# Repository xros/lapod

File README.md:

# LaPOD
LaPOD is a project to create a logic analyzer probe for the various [Rigol]
oscilloscopes that feature the logic analyzer connector. Not all scopes have
the connector exposed and not all scopes have the components needed on the
PCB. But for those that do, the LaPOD could be a cheap alternative to get
those probes.

## Scope support
Currently supported is the MSO5000 series, which feature a 50 pin IDC connector
and the DHO900, which features the same 50 pin connector, but is a bit more
narrow at the front. To cater for either needs or choice, there's two breakout
boards that feature either a full, but wider HDMI connector, or a mini HDMI
connector which makes the PCB as narrow as possible.

The idea is, to also get a 68 pin IDC connector added, but that requires
the knowledge of the pinout and someone that can validate and test the design.
The 68 pin IDC connector should have nearly the same signals however and would
fit the DS1074Z-S Plus for example.

The DS7000 and MSO8000 feature a PCI express 1x connector (34 pins), with an
unknown pinout, but the idea is that it could very much also support our pods.

## PODs
Currently, there are 3 pods available. The LMH7322 based pod, where two dual
channel chips supply 4 bits to the pod. The LMH7322 is the same chip used in
the official PLA2216 (MSO5000) and RPL1116 (DS1000Z) probes. It may also be
used on the RPL2316 (DS2000, DS7000 and MSO8000). The original probe needs 8
of these chips for 16 channels, and that brings the cost of the chips alone
up to around $75. Probably one of the reason of the high price.

Then there's also the LMH7324 based pod. Here a single quad channel chip is
used to supply the 4 bits to the pod. The LMH7324 is very closely related to
the LMH7322, but not identical. It is a little bit cheaper option and for some
signal scenarios even preferred to have the same chip handle 4 channels.

Finally, there is the SNV65LVDS based chip. It is a much cheaper chip that can
do logic signal detection, but at a very much more limited range. It also costs
considerably less. A true cheap alternative.

## Outputs
The schematics, PCB's gerbers etc are generated by the CI pipeline and can be
found under [releases](https://gitlab.com/riglol/lapod/-/releases) for tagged
builds. Tagging happens after verification however, so the release-candidates,
the files sent out to the board house for verification can be found under
[packages](https://gitlab.com/riglol/lapod/-/packages).

## Contact
Discussion about the development of these pods is held over on the
[EEVBlog forum].

[Rigol]: https://rigolna.com
[EEVBlog forum]: https://www.eevblog.com/forum/testgear/another-low-cost-la-probe-for-rigol-mso5000-by-oliv3r/

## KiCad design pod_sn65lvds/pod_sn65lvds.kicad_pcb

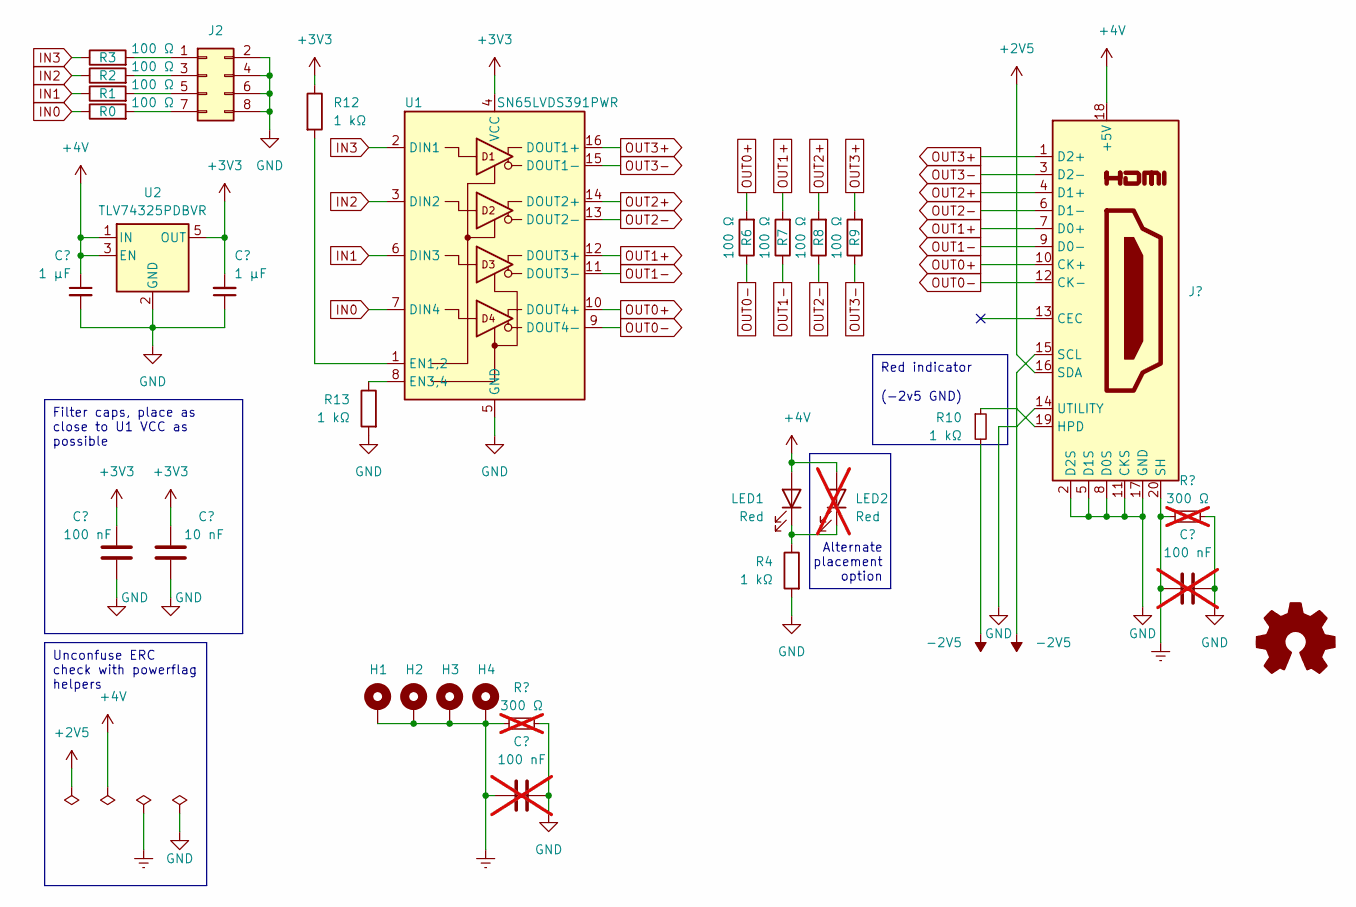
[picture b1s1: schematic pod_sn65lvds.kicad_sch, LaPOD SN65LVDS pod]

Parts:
C1, C4: 1 μF; C_0805_2012Metric_Pad1.18x1.45mm_HandSolder; tolerance 10%; LCSC C28323
C2: 100 nF; C_0805_2012Metric_Pad1.18x1.45mm_HandSolder; tolerance 10%; LCSC C49678
C3: 10 nF; C_0805_2012Metric_Pad1.18x1.45mm_HandSolder; tolerance 10%; LCSC C1710
C5, C6: 100 nF; C_0603_1608Metric_Pad1.08x0.95mm_HandSolder; tolerance 10%; LCSC C14663; not fitted
H1, H2, H3, H4: MountingHole_Pad; MountingHole_2.2mm_M2_Pad_Via
J1: HDMI_A; HDMI-SMD_HDMI-19PIN-043; LCSC C2858275
J2: Conn_02x04_Odd_Even; IDC-Header_2x04_P2.54mm_Horizontal; LCSC C9139
LED1: Red; LED_0805_2012Metric_Pad1.15x1.40mm_HandSolder; LCSC C84256
LED2: Red; LED_0805_2012Metric_Pad1.15x1.40mm_HandSolder; LCSC C84256; not fitted
R0, R1, R2, R3, R6, R7, R8, R9: 100 Ω; R_0805_2012Metric_Pad1.20x1.40mm_HandSolder; tolerance 1%; LCSC C17408
R4, R10, R12, R13: 1 kΩ; R_0805_2012Metric_Pad1.20x1.40mm_HandSolder; tolerance 1%; LCSC C17513
R5, R11: 300 Ω; R_0402_1005Metric_Pad0.72x0.64mm_HandSolder; tolerance 1%; LCSC C25102; not fitted
U1: SN65LVDS391PWR; TSSOP-16_4.4x5mm_P0.65mm; LCSC C354139
U2: TLV74325PDBVR; SOT-23-5_HandSoldering; LCSC C485154

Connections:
+2V5: J1.16 (SDA)
+3V3: C2.1, C3.1, C4.2, R12.1, U1.4 (VCC), U2.5 (OUT)
+4V: C1.1, J1.18 (+5V), LED1.2 (A), LED2.2 (A), U2.1 (IN), U2.3 (EN)
-2V5: J1.15 (SCL), R10.2
Earth: C5.2, C6.2, H1.1, H2.1, H3.1, H4.1, J1.20 (SH), R5.2, R11.2
GND: C1.2, C2.2, C3.2, C4.1, C5.1, C6.1, J1.2 (D2S), J1.5 (D1S), J1.8 (D0S), J1.11 (CKS), J1.14 (UTILITY), J1.17 (GND), J2.2, J2.4, J2.6, J2.8, R4.2, R5.1, R11.1, R13.2, U1.5 (GND), U2.2 (GND)
IN0: R0.1, U1.7 (DIN4)
IN1: R1.1, U1.6 (DIN3)
IN2: R2.1, U1.3 (DIN2)
IN3: R3.1, U1.2 (DIN1)
unnamed: J1.19 (HPD), R10.1
unnamed: J2.1, R3.2
unnamed: J2.3, R2.2
unnamed: J2.5, R1.2
unnamed: J2.7, R0.2
unnamed: LED1.1 (K), LED2.1 (K), R4.1
unnamed: R12.2, U1.1 (EN1,2)
unnamed: R13.1, U1.8 (EN3,4)
OUT0+: J1.10 (CK+), R6.2, U1.10 (DOUT4+)
OUT0-: J1.12 (CK-), R6.1, U1.9 (DOUT4-)
OUT1+: J1.7 (D0+), R7.2, U1.12 (DOUT3+)
OUT1-: J1.9 (D0-), R7.1, U1.11 (DOUT3-)
OUT2+: J1.4 (D1+), R8.2, U1.14 (DOUT2+)
OUT2-: J1.6 (D1-), R8.1, U1.13 (DOUT2-)
OUT3+: J1.1 (D2+), R9.2, U1.16 (DOUT1+)
OUT3-: J1.3 (D2-), R9.1, U1.15 (DOUT1-)

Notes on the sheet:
Alternate placement option
Red indicator (-2v5 GND)
Filter caps, place as close to U1 VCC as possible
Unconfuse ERC check with powerflag helpers

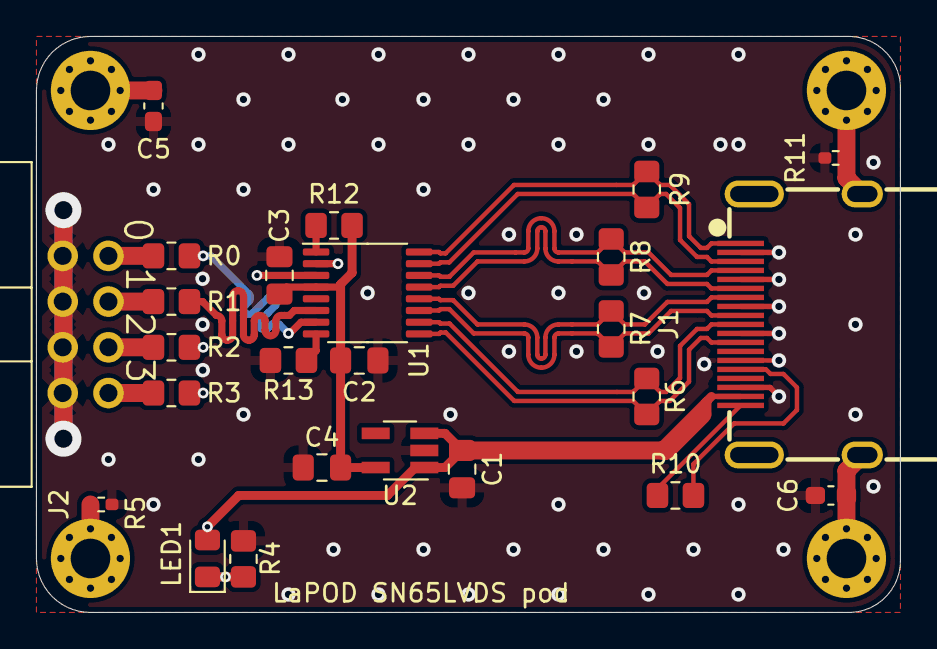
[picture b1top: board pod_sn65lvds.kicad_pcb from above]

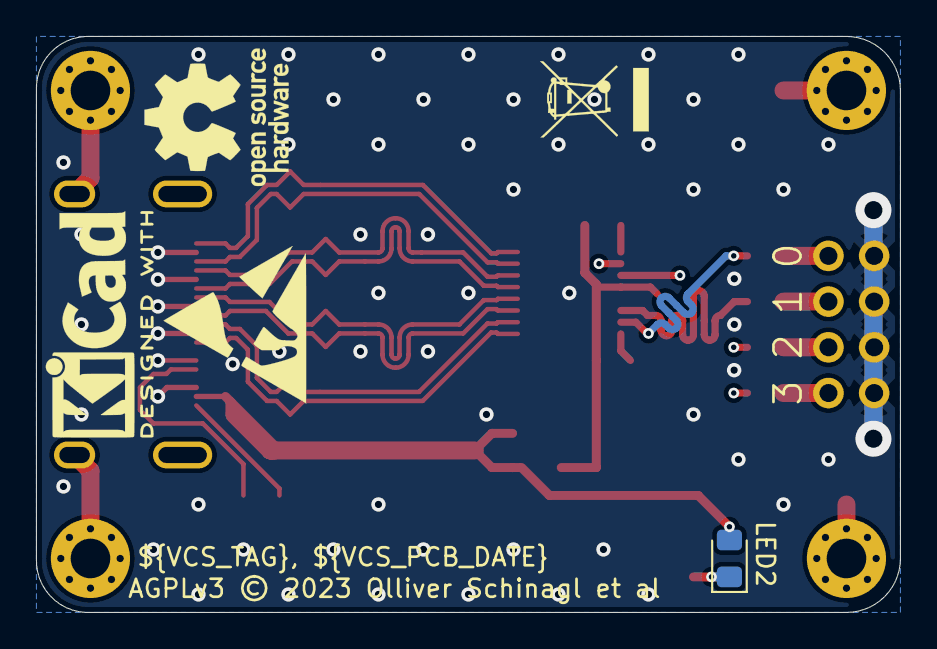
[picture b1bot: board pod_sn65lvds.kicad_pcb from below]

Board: 4 copper layers, 48.0 x 32.0 mm, 34 parts (5 on the bottom side), 25 nets.

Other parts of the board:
LG1: ESD-Logo_8.9x8mm_SilkScreen
LG2: KiCad-Logo2_5mm_SilkScreen
LG3: OSHW-Logo_7.5x8mm_SilkScreen
LG4: WEEE-Logo_4.2x6mm_SilkScreen

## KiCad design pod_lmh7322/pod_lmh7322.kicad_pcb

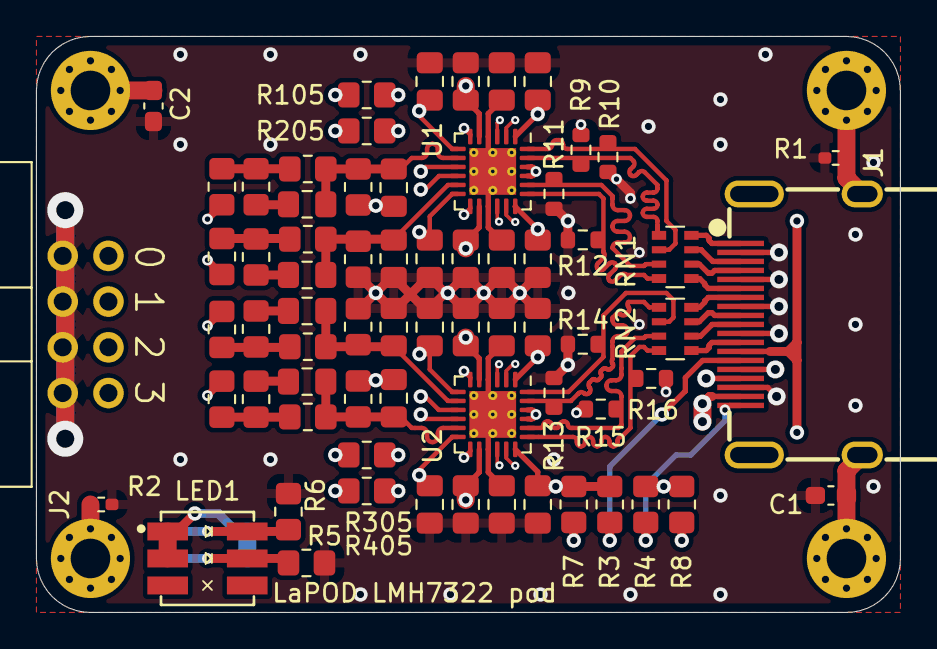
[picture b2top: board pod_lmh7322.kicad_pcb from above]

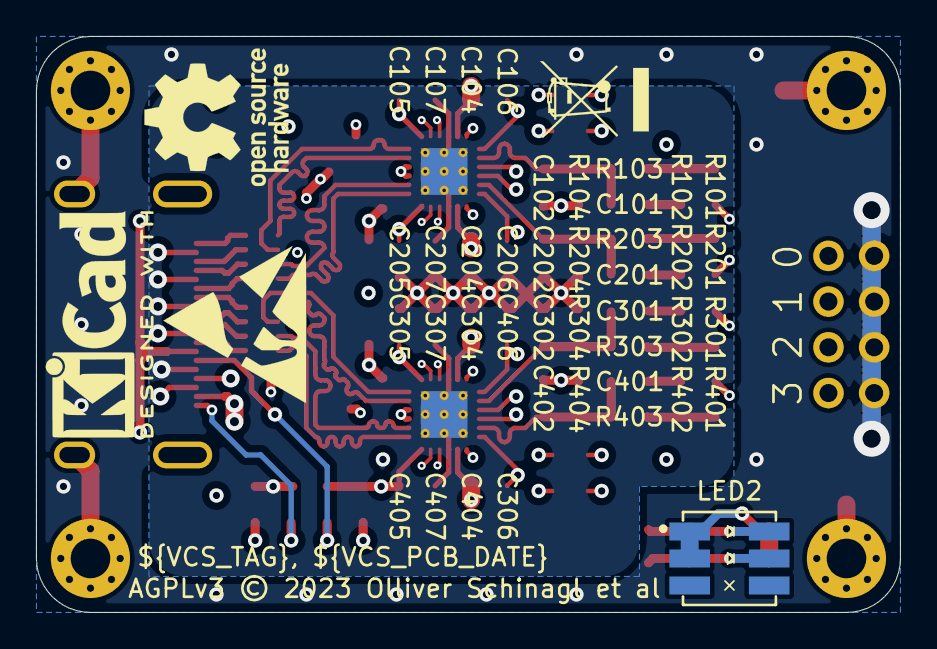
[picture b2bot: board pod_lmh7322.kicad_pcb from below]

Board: 4 copper layers, 48.0 x 32.0 mm, 78 parts (5 on the bottom side), 52 nets.

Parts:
C1, C2: 100 nF; C_0603_1608Metric_Pad1.08x0.95mm_HandSolder
C101, C201, C301, C401: 3.3 pF; C_0805_2012Metric_Pad1.18x1.45mm_HandSolder
C102, C202, C302, C402: 27 pF; C_0805_2012Metric_Pad1.18x1.45mm_HandSolder
C104, C105, C107, C204, C205, C207, C304, C305, C307, C404, C405, C407: 100 nF; C_0805_2012Metric_Pad1.18x1.45mm_HandSolder
C106, C206, C306, C406: 10 nF; C_0805_2012Metric_Pad1.18x1.45mm_HandSolder
H1, H2, H3, H4: MountingHole_Pad; MountingHole_2.2mm_M2_Pad_Via
J1: HDMI_A; HDMI-SMD_HDMI-19PIN-043
J2: Conn_02x04_Odd_Even; IDC-Header_2x04_P2.54mm_Horizontal
LED1, LED2: TC5050RGBF08-3CJH-AF53A; LED-SMD_6P-L5.0-W5.0-TL_TC5050RGBF08
LG1: ESD-Logo_8.9x8mm_SilkScreen
LG2: KiCad-Logo2_5mm_SilkScreen
LG3: OSHW-Logo_7.5x8mm_SilkScreen
LG4: WEEE-Logo_4.2x6mm_SilkScreen
R1, R2: 300 Ω; R_0402_1005Metric_Pad0.72x0.64mm_HandSolder
R3, R4, R5, R6, R7, R8: 1 kΩ; R_0805_2012Metric_Pad1.20x1.40mm_HandSolder
R9, R10, R11, R12, R13, R14, R15, R16: 220 Ω; R_0603_1608Metric
R101, R201, R301, R401: 300 Ω; R_0805_2012Metric_Pad1.20x1.40mm_HandSolder
R102, R202, R302, R402: 499 Ω; R_0805_2012Metric_Pad1.20x1.40mm_HandSolder
R103, R203, R303, R403: 90.9 kΩ; R_0805_2012Metric_Pad1.20x1.40mm_HandSolder
R104, R105, R204, R205, R304, R305, R404, R405: 10 kΩ; R_0805_2012Metric_Pad1.20x1.40mm_HandSolder
RN1, RN2: 49.9 Ω; R_Array_Convex_4x0603
U1, U2: LMH7322; WQFN-24-1EP_4x4mm_P0.5mm_EP2.6x2.6mm_ThermalVias

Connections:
+2V5: C105.1, C205.1, C305.1, C405.1, J1.16 (SDA), R3.1, R7.1, U1.1 (VCCO), U1.18 (VCCO), U1.21 (VCCO), U1.22 (VCCO), U2.1 (VCCO), U2.18 (VCCO), U2.21 (VCCO), U2.22 (VCCO)
+4V: C104.1, C204.1, C304.1, C404.1, J1.18 (+5V), LED1.1 (+), LED1.2 (+), LED2.1 (+), LED2.2 (+), U1.5 (VCCI), U1.14 (VCCI), U2.5 (VCCI), U2.14 (VCCI)
-2V5: C107.1, C207.1, C307.1, C407.1, J1.15 (SCL), R4.2, R8.2, U1.4 (VEE), U1.15 (VEE), U1.25 (VEE/EP), U2.4 (VEE), U2.15 (VEE), U2.25 (VEE/EP)
Earth: C1.2, C2.2, H1.1, H2.1, H3.1, H4.1, J1.20 (SH), R1.2, R2.2
GND: C1.1, C2.1, C102.1, C104.2, C105.2, C106.1, C107.2, C202.1, C204.2, C205.2, C206.1, C207.2, C302.1, C304.2, C305.2, C306.1, C307.2, C402.1, C404.2, C405.2, C406.1, C407.2, J1.2 (D2S), J1.5 (D1S), J1.8 (D0S), J1.11 (CKS), J1.17 (GND), J2.2, J2.4, J2.6, J2.8, R1.1, R2.1, R5.2, R6.2, R9.2, R10.2, R11.2, R12.2, R13.2, R14.2, R15.2, R16.2, R104.2, R204.2, R304.2, R404.2
IN0: J2.7, R401.2
IN1: J2.5, R301.2
IN2: J2.3, R201.2
IN3: J2.1, R101.2
LEB: R8.1, U1.2 (LE), U1.17 (LE), U2.2 (LE), U2.17 (LE)
unnamed: C101.1, R102.1
unnamed: C201.1, R202.1
unnamed: C301.1, R302.1
unnamed: C401.1, R402.1
unnamed: J1.10 (CK+), RN2.6 (R3.2)
unnamed: J1.12 (CK-), RN2.5 (R4.2)
unnamed: J1.7 (D0+), RN2.8 (R1.2)
unnamed: J1.9 (D0-), RN2.7 (R2.2)
unnamed: J1.4 (D1+), RN1.6 (R3.2)
unnamed: J1.6 (D1-), RN1.5 (R4.2)
unnamed: J1.1 (D2+), RN1.8 (R1.2)
unnamed: J1.3 (D2-), RN1.7 (R2.2)
unnamed: J1.19 (HPD), R4.1
unnamed: J1.14 (UTILITY), R3.2
unnamed: LED1.5 (-), LED2.5 (-), R5.1
unnamed: LED1.6 (-), LED2.6 (-), R6.1
unnamed: R101.1, R102.2, R103.1
unnamed: R201.1, R202.2, R203.1
unnamed: R301.1, R302.2, R303.1
unnamed: R401.1, R402.2, R403.1
unnamed: C101.2, C102.2, R103.2, R104.1, U1.8 (+)
unnamed: R105.2, U1.9 (RHREF)
unnamed: R105.1, U1.6 (RHYS)
unnamed: C201.2, C202.2, R203.2, R204.1, U1.11 (+)
unnamed: R205.2, U1.10 (RHREF)
unnamed: R205.1, U1.13 (RHYS)
unnamed: C301.2, C302.2, R303.2, R304.1, U2.8 (+)
unnamed: R305.2, U2.9 (RHREF)
unnamed: R305.1, U2.6 (RHYS)
unnamed: C401.2, C402.2, R403.2, R404.1, U2.11 (+)
unnamed: R405.2, U2.10 (RHREF)
unnamed: R405.1, U2.13 (RHYS)
OUT0+: R15.1, RN2.3 (R3.1), U2.20 (Q)
OUT0-: R16.1, RN2.4 (R4.1), U2.19 (~Q)
OUT1+: R13.1, RN2.1 (R1.1), U2.23 (Q)
OUT1-: R14.1, RN2.2 (R2.1), U2.24 (~Q)
OUT2+: R11.1, RN1.3 (R3.1), U1.20 (Q)
OUT2-: R12.1, RN1.4 (R4.1), U1.19 (~Q)
OUT3+: R9.1, RN1.1 (R1.1), U1.23 (Q)
OUT3-: R10.1, RN1.2 (R2.1), U1.24 (~Q)
VREF: C106.2, C206.2, C306.2, C406.2, J1.13 (CEC), U1.7 (-), U1.12 (-), U2.7 (-), U2.12 (-)
~LEB: R7.2, U1.3 (~LE), U1.16 (~LE), U2.3 (~LE), U2.16 (~LE)

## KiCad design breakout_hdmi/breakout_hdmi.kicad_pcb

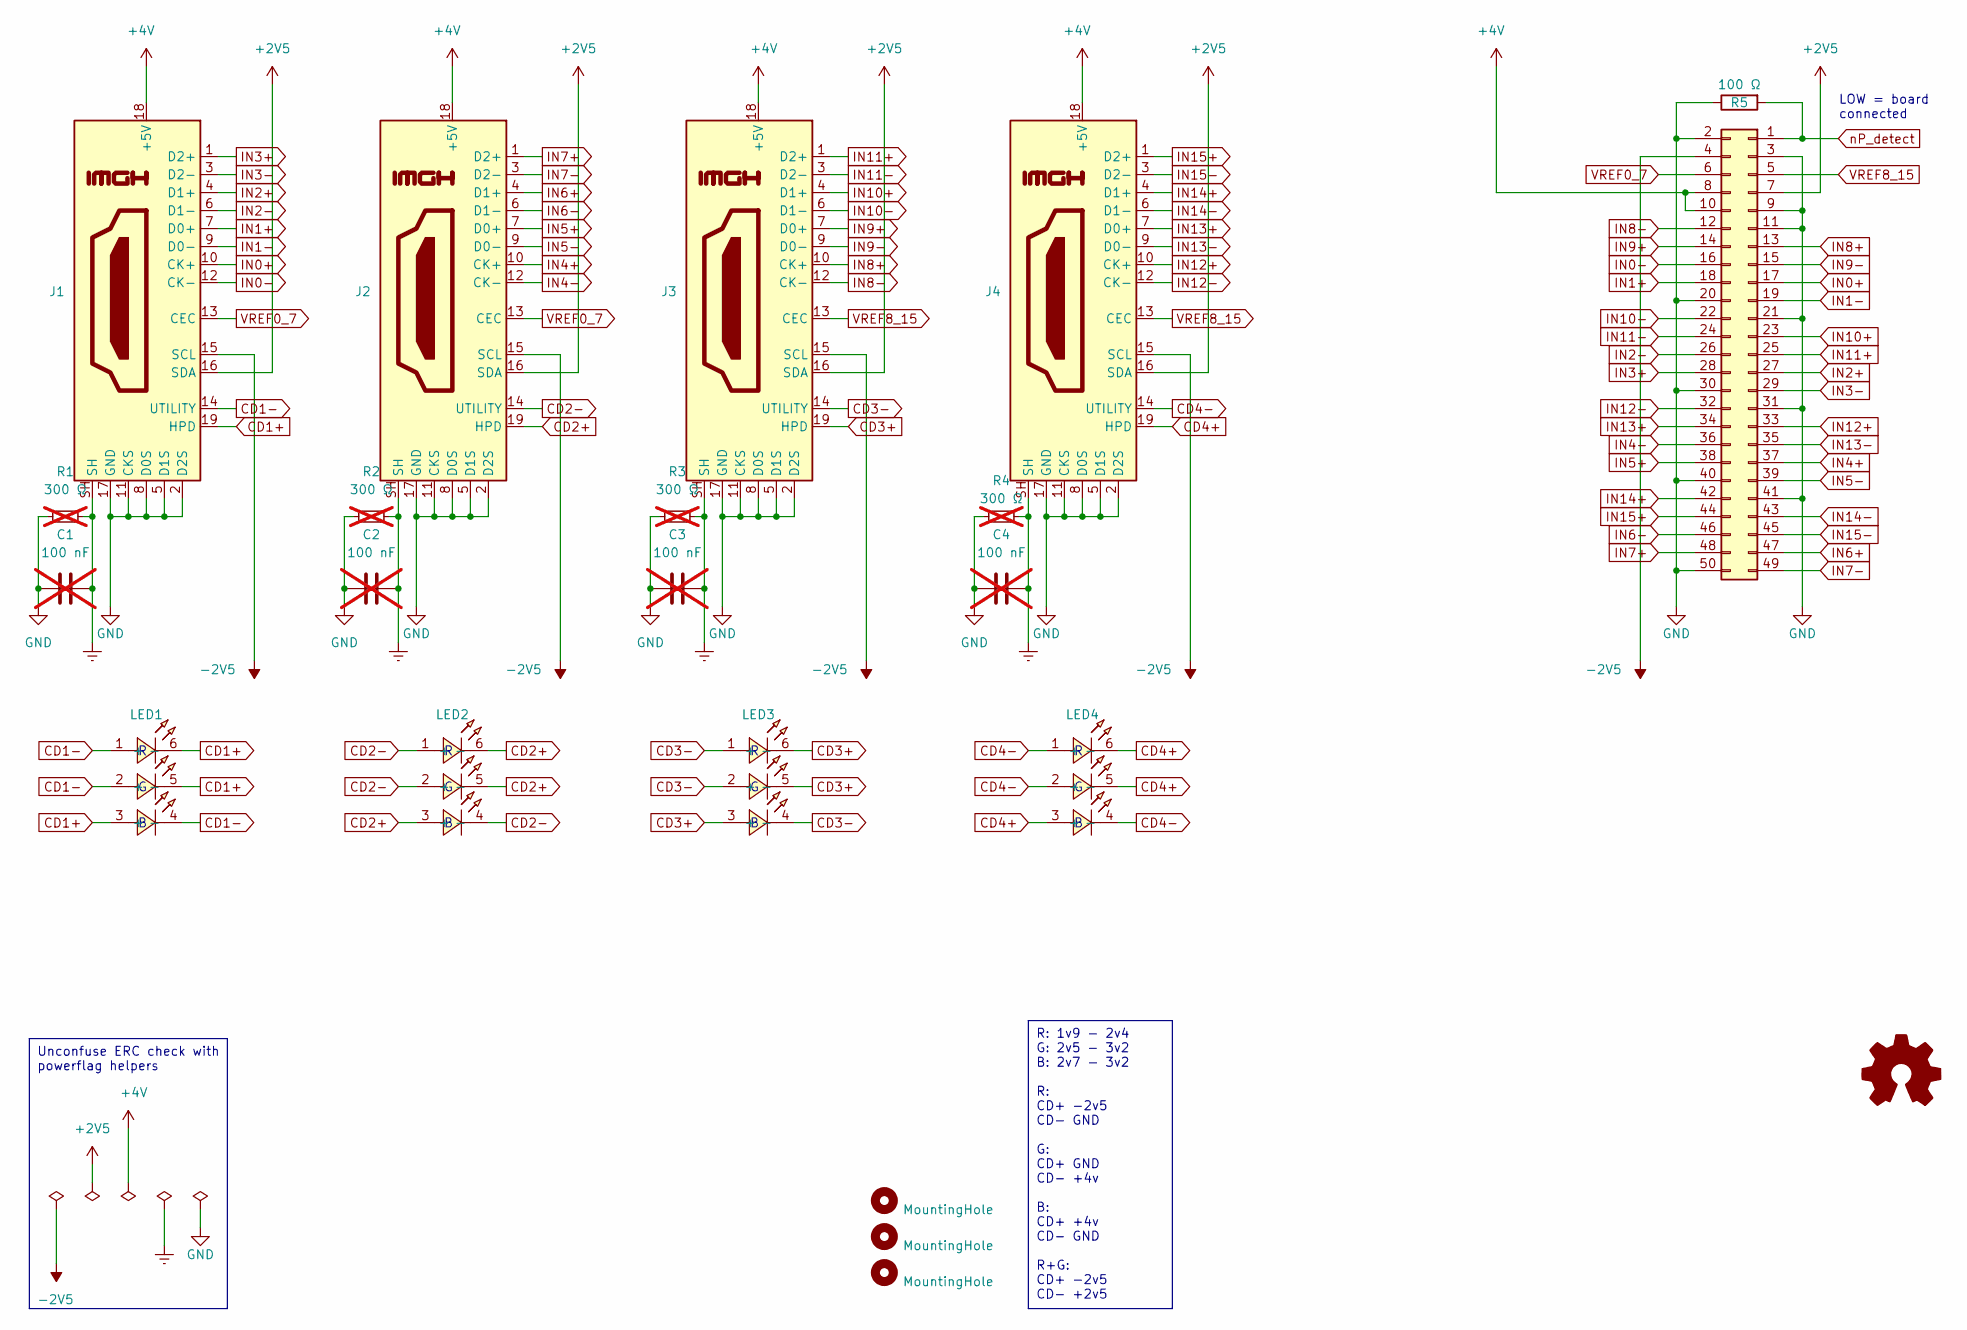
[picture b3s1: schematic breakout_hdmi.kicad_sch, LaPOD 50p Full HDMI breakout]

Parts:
C1, C2, C3, C4: 100 nF; C_0603_1608Metric_Pad1.08x0.95mm_HandSolder; tolerance 10%; voltage 50 V; LCSC C14663; not fitted
H1, H2, H3: MountingHole; MountingHole_2.2mm_M2_DIN965
J1, J2, J3, J4: HDMI_A; HDMI-SMD_HDMI-19PIN-043; LCSC C2858275
J5: Conn_02x25; IDC-Header_2x25_P2.54mm_Vertical_SMD; LCSC C350296
LED1, LED2, LED3, LED4: TC5050RGBF08-3CJH-AF53A; LED-SMD_6P-L5.0-W5.0-TL_TC5050RGBF08; LCSC C784540
R1, R2, R3, R4: 300 Ω; R_0402_1005Metric_Pad0.72x0.64mm_HandSolder; tolerance 1%; LCSC C25102; not fitted
R5: 100 Ω; R_0805_2012Metric_Pad1.20x1.40mm_HandSolder; tolerance 1%; LCSC C17408

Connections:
+2V5: J1.16 (SDA), J2.16 (SDA), J3.16 (SDA), J4.16 (SDA), J5.7
+4V: J1.18 (+5V), J2.18 (+5V), J3.18 (+5V), J4.18 (+5V), J5.8, J5.10
-2V5: J1.15 (SCL), J2.15 (SCL), J3.15 (SCL), J4.15 (SCL), J5.4
CD1+: J1.19 (HPD), LED1.3 (+), LED1.5 (-), LED1.6 (-)
CD1-: J1.14 (UTILITY), LED1.1 (+), LED1.2 (+), LED1.4 (-)
CD2+: J2.19 (HPD), LED2.3 (+), LED2.5 (-), LED2.6 (-)
CD2-: J2.14 (UTILITY), LED2.1 (+), LED2.2 (+), LED2.4 (-)
CD3+: J3.19 (HPD), LED3.3 (+), LED3.5 (-), LED3.6 (-)
CD3-: J3.14 (UTILITY), LED3.1 (+), LED3.2 (+), LED3.4 (-)
CD4+: J4.19 (HPD), LED4.3 (+), LED4.5 (-), LED4.6 (-)
CD4-: J4.14 (UTILITY), LED4.1 (+), LED4.2 (+), LED4.4 (-)
Earth: C1.2, C2.2, C3.2, C4.2, J1.SH, J2.SH, J3.SH, J4.SH, R1.2, R2.2, R3.2, R4.2
GND: C1.1, C2.1, C3.1, C4.1, J1.2 (D2S), J1.5 (D1S), J1.8 (D0S), J1.11 (CKS), J1.17 (GND), J2.2 (D2S), J2.5 (D1S), J2.8 (D0S), J2.11 (CKS), J2.17 (GND), J3.2 (D2S), J3.5 (D1S), J3.8 (D0S), J3.11 (CKS), J3.17 (GND), J4.2 (D2S), J4.5 (D1S), J4.8 (D0S), J4.11 (CKS), J4.17 (GND), J5.2, J5.3, J5.9, J5.11, J5.20, J5.21, J5.30, J5.31, J5.40, J5.41, J5.50, R1.1, R2.1, R3.1, R4.1, R5.1
IN0+: J1.10 (CK+), J5.17
IN0-: J1.12 (CK-), J5.16
IN1+: J1.7 (D0+), J5.18
IN1-: J1.9 (D0-), J5.19
IN2+: J1.4 (D1+), J5.27
IN2-: J1.6 (D1-), J5.26
IN3+: J1.1 (D2+), J5.28
IN3-: J1.3 (D2-), J5.29
IN4+: J2.10 (CK+), J5.37
IN4-: J2.12 (CK-), J5.36
IN5+: J2.7 (D0+), J5.38
IN5-: J2.9 (D0-), J5.39
IN6+: J2.4 (D1+), J5.47
IN6-: J2.6 (D1-), J5.46
IN7+: J2.1 (D2+), J5.48
IN7-: J2.3 (D2-), J5.49
IN8+: J3.10 (CK+), J5.13
IN8-: J3.12 (CK-), J5.12
IN9+: J3.7 (D0+), J5.14
IN9-: J3.9 (D0-), J5.15
IN10+: J3.4 (D1+), J5.23
IN10-: J3.6 (D1-), J5.22
IN11+: J3.1 (D2+), J5.25
IN11-: J3.3 (D2-), J5.24
IN12+: J4.10 (CK+), J5.33
IN12-: J4.12 (CK-), J5.32
IN13+: J4.7 (D0+), J5.34
IN13-: J4.9 (D0-), J5.35
IN14+: J4.4 (D1+), J5.42
IN14-: J4.6 (D1-), J5.43
IN15+: J4.1 (D2+), J5.44
IN15-: J4.3 (D2-), J5.45
VREF0_7: J1.13 (CEC), J2.13 (CEC), J5.6
VREF8_15: J3.13 (CEC), J4.13 (CEC), J5.5
nP_detect: J5.1, R5.2

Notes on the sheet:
R: 1v9 - 2v4 G: 2v5 - 3v2 B: 2v7 - 3v2 R: CD+ -2v5 CD- GND G: CD+ GND CD- +4v B: CD+ +4v CD- GND R+G: CD+ -2v5 CD- +2v5
Unconfuse ERC check with powerflag helpers
LOW = board connected

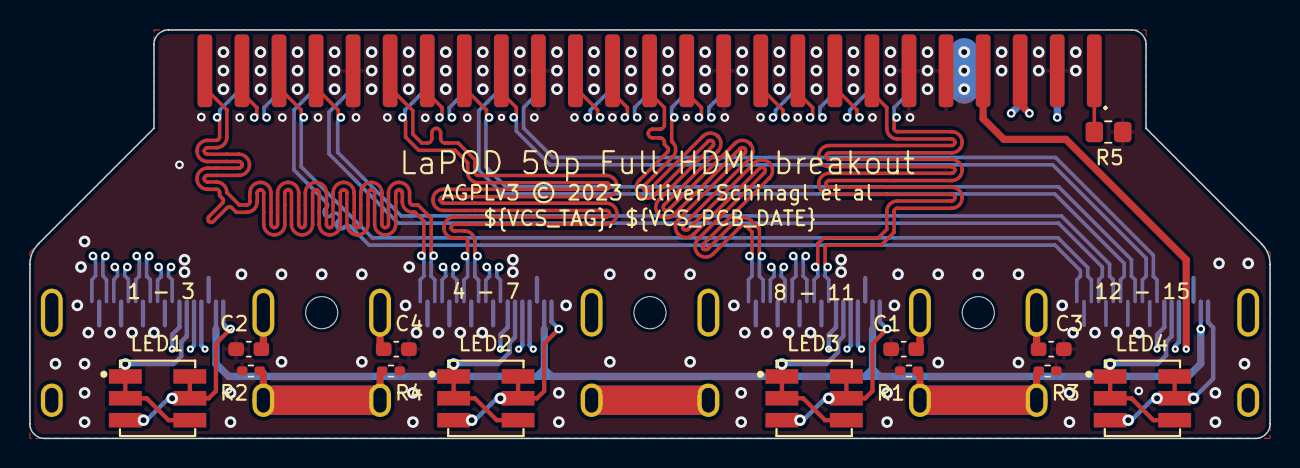
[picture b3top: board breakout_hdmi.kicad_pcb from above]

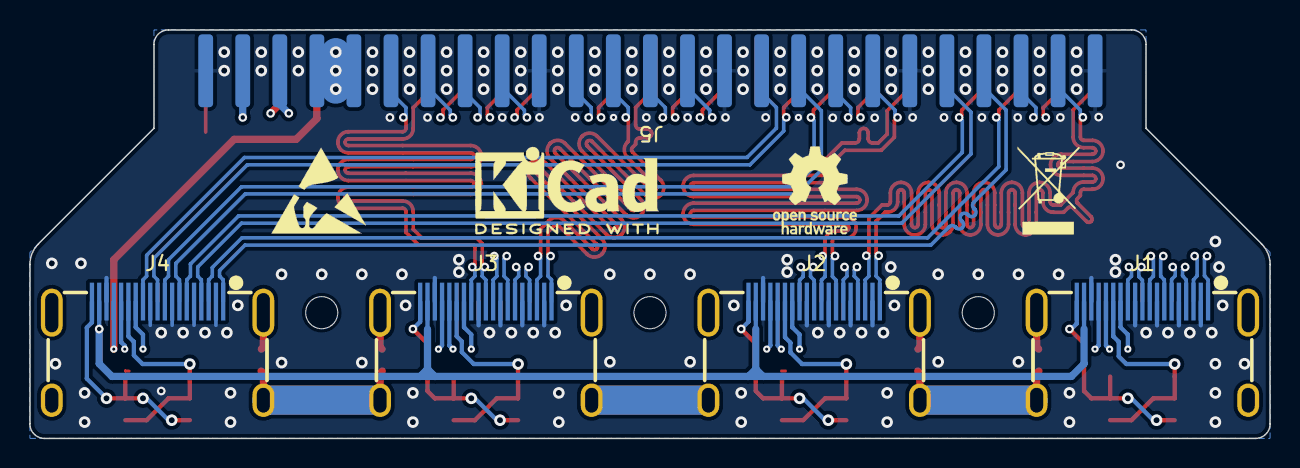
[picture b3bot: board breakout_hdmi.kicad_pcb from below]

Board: 4 copper layers, 85.0 x 28.0 mm, 25 parts (8 on the bottom side), 48 nets.

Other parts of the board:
LG1: OSHW-Logo_5.7x6mm_SilkScreen
LG2: KiCad-Logo2_5mm_SilkScreen
LG3: ESD-Logo_6.6x6mm_SilkScreen
LG4: WEEE-Logo_4.2x6mm_SilkScreen

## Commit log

2023-12-09 license: Add initial AGPL-3+ license
2023-12-09 gitignore: Ignore editor related files
2023-12-09 editorconfig: Add initial .editorconfig
    This ensures our codestyle is consistent throughout
2024-01-23 git: Enable LFS for PDF files
    No need to track datasheets.
2024-01-23 CI: Use git compatible worksheet
    The built-in worksheet doesn't deal with git versions etc very well.
    While we could encode this information in the 'rev' box, it is too small.
    So instead of hacking around the shortcommings of the default worksheet,
    lets do our own.
    One problem remains, is that SHEETPATH and SHEETNAME are the two
    variables used to name a SHEET. Because they are used mutually
2024-01-23 gitignore: Ignore KiCad generated temporary files
2024-01-23 lapod: Add initial breakout_hdmi project
    This adds an empty project, so we can start setting up pipelines etc,
    and have a base to work with.
2024-02-03 gitignore: Ignore KiBot generated temporary files
2024-02-03 kici: Add KiCi submodule for KiBot jobs
    To be able to easily access and update the common KiBot jobs offered by
    KiCi, its easiest to add the repository as a submodule.
2024-02-03 CI: Add basic pipelines
    This sets up our pipeline scaffolding, not doing much yet but run some
    basic linters. Adding the rest of the pipeline will be a triviality
    after this however.
2024-02-03 lapod: Add 50p full HDMI breakout board
    The first component of the LaPOD, the HDMI breakout board. Takes the 50
    pin Rigol connector, and converts it to 4 full HDMI ports.
2024-02-03 lapod: Add 50p mini HDMI breakout board
    Like the regular HDMI breakout board, this is the same board, but with
    mini-hdmi connectors, to make for a smaller width, fitting better in
    some scopes.
2024-02-03 lapod: Add LMH7322 based pod
    This commit adds the LMH7322 based pod. This pod is based on two dual
    opamps and uses two of these chips.
    This is the same chip the official rigol probe also uses. One of their
    pods contains 8 chips (4 on each side).
    As an option, only 1 LMH7322 can be used to only use a dual output, if
    heat and cost are an issue.
2024-02-03 lapod: Add LMH7324 based pod
    This commit adds the LMH7324 based pod. This pod is based on one quad
    opamp, potentially making the pod cheaper.
    Heat distribution should also be better, as there's more copper for just
    the one chip.
2024-02-03 lapod: Add SNV65LVDS based pod
    This commit adds the SNV65LVDS based pod. This pod is based on one quad
    opamp, but without the wide input range of the LMH732x parts, making it
    considerable cheaper.
    The BOM currently uses the SVN65LVCDS and TLV743P LDO, which limits the
    input range from 1v6 to 5v5 logic levels, which for most applications is
    perfectly fine for most applications, but alternative parts should fit
2024-02-03 doc: Add initial README
    Just some basic info, will grow over time.
2024-02-03 Changelog: Auto-generate new 'CHANGELOG.md'
2024-02-24 boyscout: Properly name GND zone in pcb
    No functional changes, this is just for consistency.
2024-02-24 fix: Replace SN65LVDS31D/SN65LVDS047W with SN65LVDS391PWR
    We accidentally used the incorrect LVDS comparator. The difference is
    subtle, but important.
    The symbol came from the KiCad default library, the rest of the part
    number from LCSC, but was simply the wrong one. 31D vs 391PWR. Subtle
    but important.
    Luckily, the footprint was almost the same, so no real changes where needed
2024-02-28 kici: Update to version 0.4.2
    The new version of KiCi fixes a bunch of bugs, and brings us navigate and present.
2024-03-07 kibot: Switch to 1.6.5
    There's a cascading bug which break the pipeline currently. One is the
    fact that solder paste does not clear the underlying solder mask
    underneath it explicitly. However clearing it causes the DRC to complain
    where it says two layers are now clearing the same soldermask.
    Upgrading to the unreleased kibot 1.6.5 fixes this, but introduces a new
    problem with the kici render3d template, as the kibot changed its

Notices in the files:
breakout_hdmi/breakout_hdmi.kicad_pcb:
AGPLv3 © 2023 Olliver Schinagl et al
